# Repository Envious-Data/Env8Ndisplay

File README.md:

# Env8Ndisplay
 A 40x7 display using x4 is37fl3130

## Info:
I designed a clock a while ago using 8x LTP-305s, LTP-305s and TIL-305s are both discontinued but I made a PCBA replica called DIY305, Ive also just put LEDs on a PCB in the same arangement which this repo is one of them.

I quite like character displays which is why I made this one, there is some demo code in the firmware folder that makes use of the pico SDK so wire it up to the a pico making sure VCC goes to 3V3 and not VBUS or VSYS unless you want to use a level shifter, a number of ICs can handle different logic level voltage if needed but this one tends to glitch out in my experience.

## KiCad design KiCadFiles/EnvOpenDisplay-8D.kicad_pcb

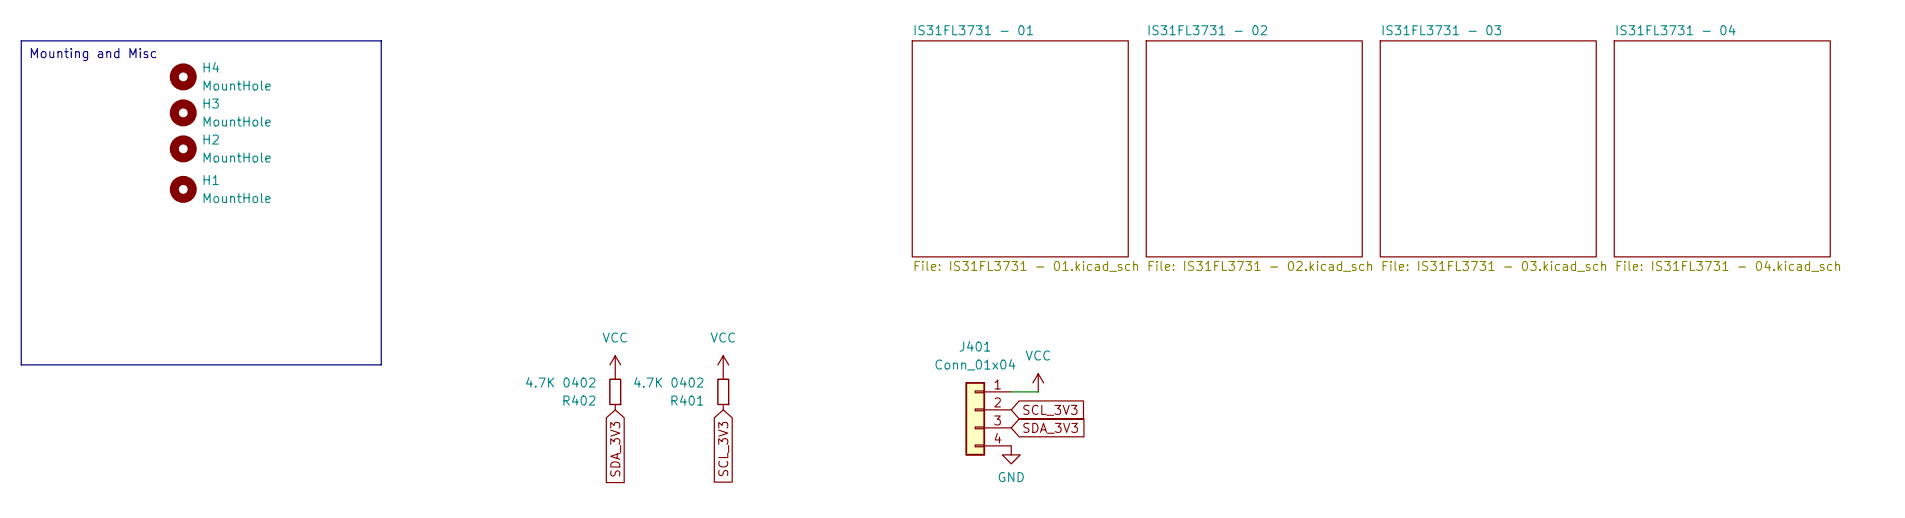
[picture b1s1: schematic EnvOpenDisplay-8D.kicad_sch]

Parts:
H1, H2, H3, H4: MountHole; MountingHole_2.2mm_M2
J401: Conn_01x04; PinSocket_1x04_P2.54mm_Vertical
R401, R402: 4.7K 0402; R_0402_1005Metric

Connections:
GND: J401.4; also elsewhere on the board
SCL_3V3: J401.2, R401.1; also elsewhere on the board
SDA_3V3: J401.3, R402.1; also elsewhere on the board
VCC: J401.1, R401.2, R402.2; also elsewhere on the board

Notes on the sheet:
Mounting and Misc

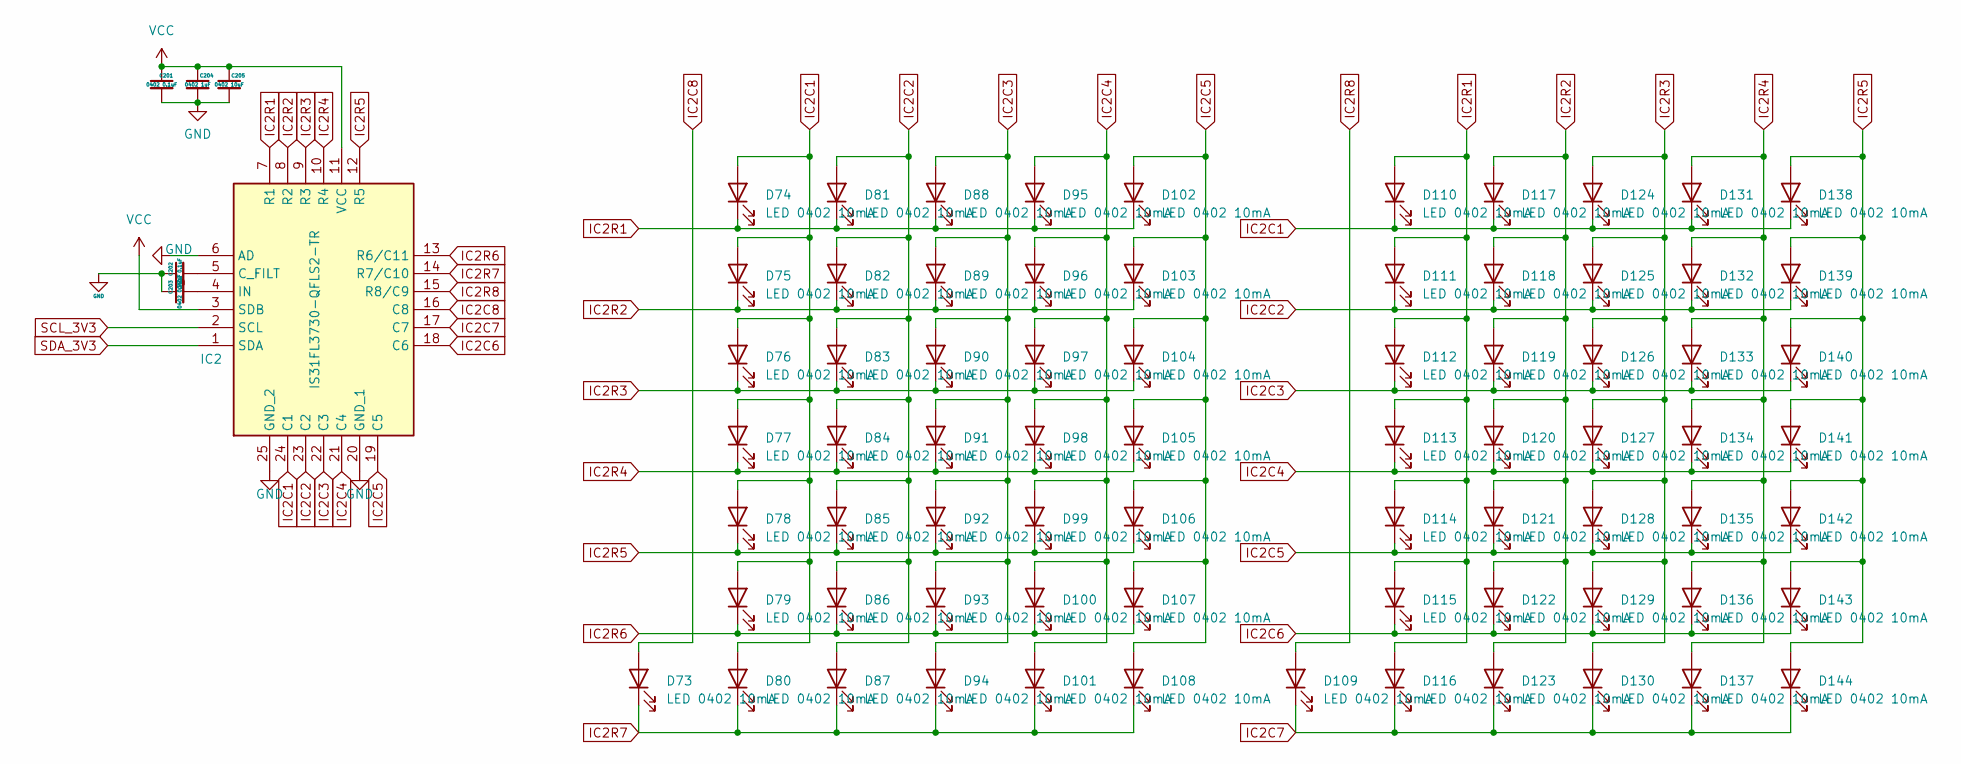
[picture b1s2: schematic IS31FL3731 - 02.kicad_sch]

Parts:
C201, C202: 0402 0.1uF; C_0402_1005Metric
C203: 0402 0.22uF; C_0402_1005Metric
C204: 0402 1uF; C_0402_1005Metric
C205: 0402 10uF; C_0402_1005Metric
D73, D74, D75, D76, D77, D78, D79, D80, D81, D82, D83, D84, D85, D86, D87, D88, D89, D90, D91, D92, D93, D94, D95, D96, D97, D98, D99, D100, D101, D102, D103, D104, D105, D106, D107, D108, D109, D110, D111, D112, D113, D114, D115, D116, D117, D118, D119, D120, D121, D122, D123, D124, D125, D126, D127, D128, D129, D130, D131, D132, D133, D134, D135, D136, D137, D138, D139, D140, D141, D142, D143, D144: LED 0402 10mA; LED_0402_1005Metric
IC2: IS31FL3730-QFLS2-TR; QFN-24-1EP_4x4mm_P0.5mm_EP2.6x2.6mm_ThermalVias; Mouser Part Number 870-IS31FL3730QFLS2R

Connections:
GND: C201.2, C202.1, C203.1, C204.2, C205.2, IC2.6 (AD), IC2.20 (GND_1), IC2.25 (GND_2); also elsewhere on the board
IC2C1: D74.2 (A), D75.2 (A), D76.2 (A), D77.2 (A), D78.2 (A), D79.2 (A), D80.2 (A), D110.1 (K), D117.1 (K), D124.1 (K), D131.1 (K), D138.1 (K), IC2.24 (C1)
IC2C2: D81.2 (A), D82.2 (A), D83.2 (A), D84.2 (A), D85.2 (A), D86.2 (A), D87.2 (A), D111.1 (K), D118.1 (K), D125.1 (K), D132.1 (K), D139.1 (K), IC2.23 (C2)
IC2C3: D88.2 (A), D89.2 (A), D90.2 (A), D91.2 (A), D92.2 (A), D93.2 (A), D94.2 (A), D112.1 (K), D119.1 (K), D126.1 (K), D133.1 (K), D140.1 (K), IC2.22 (C3)
IC2C4: D95.2 (A), D96.2 (A), D97.2 (A), D98.2 (A), D99.2 (A), D100.2 (A), D101.2 (A), D113.1 (K), D120.1 (K), D127.1 (K), D134.1 (K), D141.1 (K), IC2.21 (C4)
IC2C5: D102.2 (A), D103.2 (A), D104.2 (A), D105.2 (A), D106.2 (A), D107.2 (A), D108.2 (A), D114.1 (K), D121.1 (K), D128.1 (K), D135.1 (K), D142.1 (K), IC2.19 (C5)
IC2C6: D115.1 (K), D122.1 (K), D129.1 (K), D136.1 (K), D143.1 (K), IC2.18 (C6)
IC2C7: D109.1 (K), D116.1 (K), D123.1 (K), D130.1 (K), D137.1 (K), D144.1 (K), IC2.17 (C7)
IC2C8: D73.2 (A), IC2.16 (C8)
IC2R1: D74.1 (K), D81.1 (K), D88.1 (K), D95.1 (K), D102.1 (K), D110.2 (A), D111.2 (A), D112.2 (A), D113.2 (A), D114.2 (A), D115.2 (A), D116.2 (A), IC2.7 (R1)
IC2R2: D75.1 (K), D82.1 (K), D89.1 (K), D96.1 (K), D103.1 (K), D117.2 (A), D118.2 (A), D119.2 (A), D120.2 (A), D121.2 (A), D122.2 (A), D123.2 (A), IC2.8 (R2)
IC2R3: D76.1 (K), D83.1 (K), D90.1 (K), D97.1 (K), D104.1 (K), D124.2 (A), D125.2 (A), D126.2 (A), D127.2 (A), D128.2 (A), D129.2 (A), D130.2 (A), IC2.9 (R3)
IC2R4: D77.1 (K), D84.1 (K), D91.1 (K), D98.1 (K), D105.1 (K), D131.2 (A), D132.2 (A), D133.2 (A), D134.2 (A), D135.2 (A), D136.2 (A), D137.2 (A), IC2.10 (R4)
IC2R5: D78.1 (K), D85.1 (K), D92.1 (K), D99.1 (K), D106.1 (K), D138.2 (A), D139.2 (A), D140.2 (A), D141.2 (A), D142.2 (A), D143.2 (A), D144.2 (A), IC2.12 (R5)
IC2R6: D79.1 (K), D86.1 (K), D93.1 (K), D100.1 (K), D107.1 (K), IC2.13 (R6/C11)
IC2R7: D73.1 (K), D80.1 (K), D87.1 (K), D94.1 (K), D101.1 (K), D108.1 (K), IC2.14 (R7/C10)
IC2R8: D109.2 (A), IC2.15 (R8/C9)
unnamed: C202.2, IC2.5 (C_FILT)
unnamed: C203.2, IC2.4 (IN)
SCL_3V3: IC2.2 (SCL); also elsewhere on the board
SDA_3V3: IC2.1 (SDA); also elsewhere on the board
VCC: C201.1, C204.1, C205.1, IC2.3 (SDB), IC2.11 (VCC); also elsewhere on the board

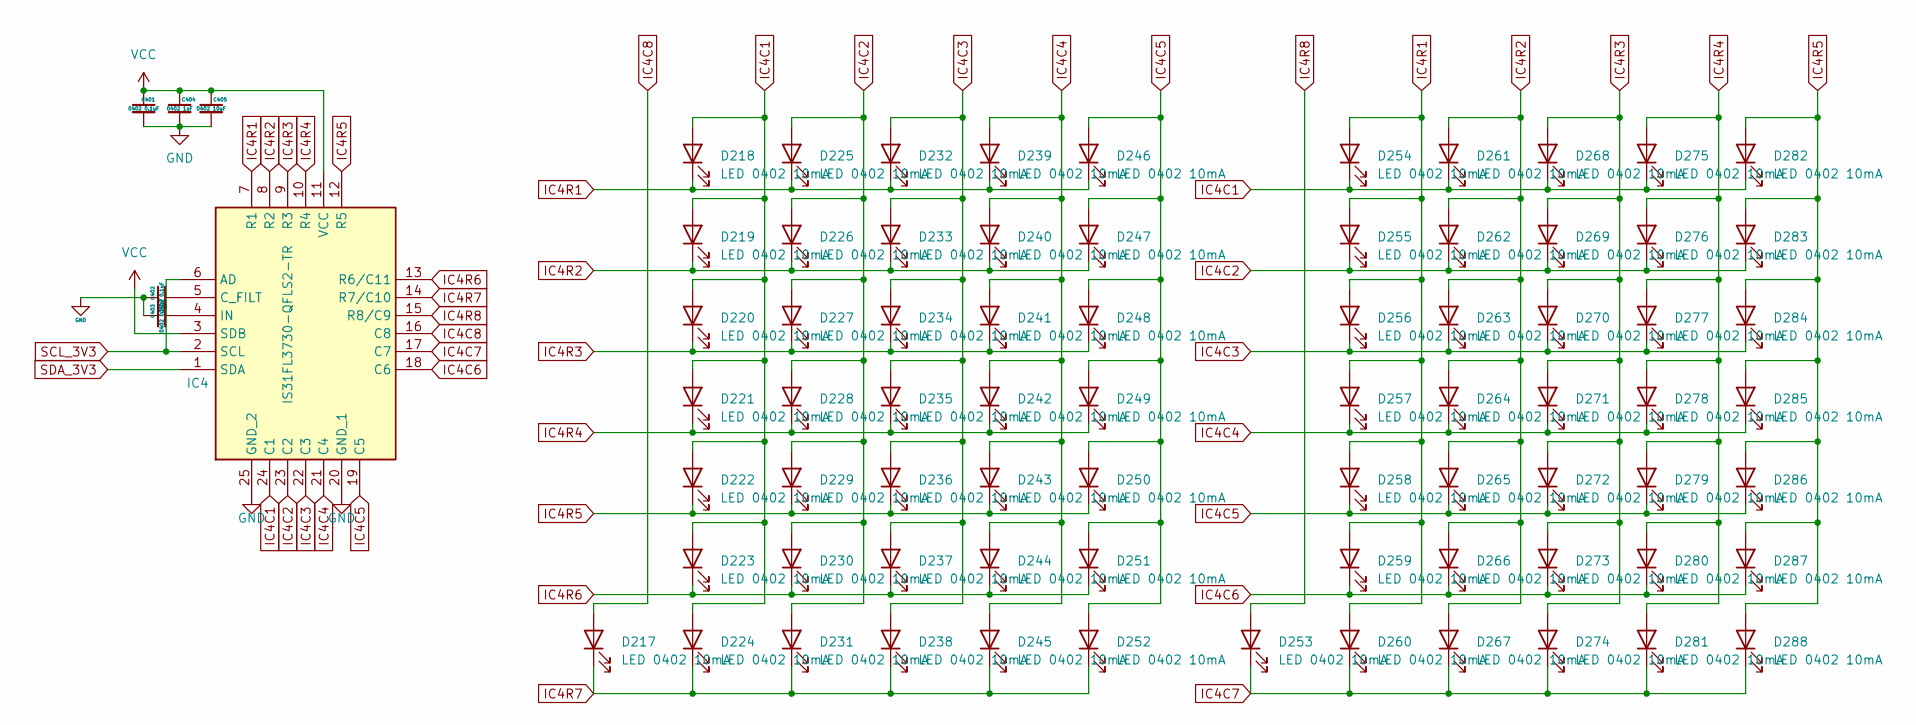
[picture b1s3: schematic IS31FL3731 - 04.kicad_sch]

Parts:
C401, C402: 0402 0.1uF; C_0402_1005Metric
C403: 0402 0.22uF; C_0402_1005Metric
C404: 0402 1uF; C_0402_1005Metric
C405: 0402 10uF; C_0402_1005Metric
D217, D218, D219, D220, D221, D222, D223, D224, D225, D226, D227, D228, D229, D230, D231, D232, D233, D234, D235, D236, D237, D238, D239, D240, D241, D242, D243, D244, D245, D246, D247, D248, D249, D250, D251, D252, D253, D254, D255, D256, D257, D258, D259, D260, D261, D262, D263, D264, D265, D266, D267, D268, D269, D270, D271, D272, D273, D274, D275, D276, D277, D278, D279, D280, D281, D282, D283, D284, D285, D286, D287, D288: LED 0402 10mA; LED_0402_1005Metric
IC4: IS31FL3730-QFLS2-TR; QFN-24-1EP_4x4mm_P0.5mm_EP2.6x2.6mm_ThermalVias; Mouser Part Number 870-IS31FL3730QFLS2R

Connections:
GND: C401.2, C402.1, C403.1, C404.2, C405.2, IC4.20 (GND_1), IC4.25 (GND_2); also elsewhere on the board
IC4C1: D218.2 (A), D219.2 (A), D220.2 (A), D221.2 (A), D222.2 (A), D223.2 (A), D224.2 (A), D254.1 (K), D261.1 (K), D268.1 (K), D275.1 (K), D282.1 (K), IC4.24 (C1)
IC4C2: D225.2 (A), D226.2 (A), D227.2 (A), D228.2 (A), D229.2 (A), D230.2 (A), D231.2 (A), D255.1 (K), D262.1 (K), D269.1 (K), D276.1 (K), D283.1 (K), IC4.23 (C2)
IC4C3: D232.2 (A), D233.2 (A), D234.2 (A), D235.2 (A), D236.2 (A), D237.2 (A), D238.2 (A), D256.1 (K), D263.1 (K), D270.1 (K), D277.1 (K), D284.1 (K), IC4.22 (C3)
IC4C4: D239.2 (A), D240.2 (A), D241.2 (A), D242.2 (A), D243.2 (A), D244.2 (A), D245.2 (A), D257.1 (K), D264.1 (K), D271.1 (K), D278.1 (K), D285.1 (K), IC4.21 (C4)
IC4C5: D246.2 (A), D247.2 (A), D248.2 (A), D249.2 (A), D250.2 (A), D251.2 (A), D252.2 (A), D258.1 (K), D265.1 (K), D272.1 (K), D279.1 (K), D286.1 (K), IC4.19 (C5)
IC4C6: D259.1 (K), D266.1 (K), D273.1 (K), D280.1 (K), D287.1 (K), IC4.18 (C6)
IC4C7: D253.1 (K), D260.1 (K), D267.1 (K), D274.1 (K), D281.1 (K), D288.1 (K), IC4.17 (C7)
IC4C8: D217.2 (A), IC4.16 (C8)
IC4R1: D218.1 (K), D225.1 (K), D232.1 (K), D239.1 (K), D246.1 (K), D254.2 (A), D255.2 (A), D256.2 (A), D257.2 (A), D258.2 (A), D259.2 (A), D260.2 (A), IC4.7 (R1)
IC4R2: D219.1 (K), D226.1 (K), D233.1 (K), D240.1 (K), D247.1 (K), D261.2 (A), D262.2 (A), D263.2 (A), D264.2 (A), D265.2 (A), D266.2 (A), D267.2 (A), IC4.8 (R2)
IC4R3: D220.1 (K), D227.1 (K), D234.1 (K), D241.1 (K), D248.1 (K), D268.2 (A), D269.2 (A), D270.2 (A), D271.2 (A), D272.2 (A), D273.2 (A), D274.2 (A), IC4.9 (R3)
IC4R4: D221.1 (K), D228.1 (K), D235.1 (K), D242.1 (K), D249.1 (K), D275.2 (A), D276.2 (A), D277.2 (A), D278.2 (A), D279.2 (A), D280.2 (A), D281.2 (A), IC4.10 (R4)
IC4R5: D222.1 (K), D229.1 (K), D236.1 (K), D243.1 (K), D250.1 (K), D282.2 (A), D283.2 (A), D284.2 (A), D285.2 (A), D286.2 (A), D287.2 (A), D288.2 (A), IC4.12 (R5)
IC4R6: D223.1 (K), D230.1 (K), D237.1 (K), D244.1 (K), D251.1 (K), IC4.13 (R6/C11)
IC4R7: D217.1 (K), D224.1 (K), D231.1 (K), D238.1 (K), D245.1 (K), D252.1 (K), IC4.14 (R7/C10)
IC4R8: D253.2 (A), IC4.15 (R8/C9)
unnamed: C402.2, IC4.5 (C_FILT)
unnamed: C403.2, IC4.4 (IN)
SCL_3V3: IC4.2 (SCL), IC4.6 (AD); also elsewhere on the board
SDA_3V3: IC4.1 (SDA); also elsewhere on the board
VCC: C401.1, C404.1, C405.1, IC4.3 (SDB), IC4.11 (VCC); also elsewhere on the board

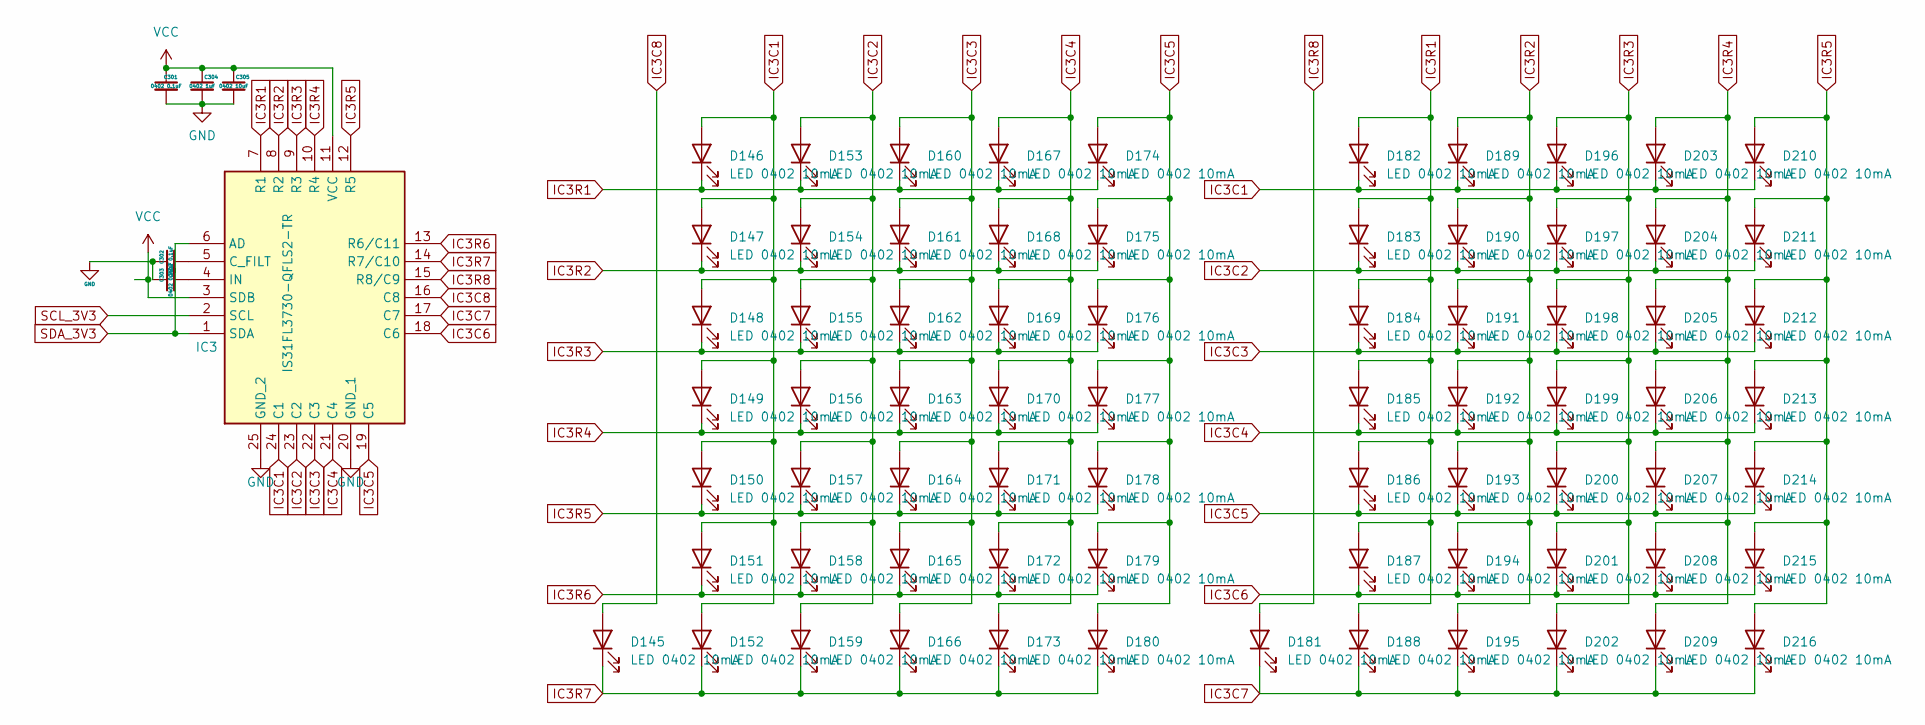
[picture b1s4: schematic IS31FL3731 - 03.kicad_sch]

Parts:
C301, C302: 0402 0.1uF; C_0402_1005Metric
C303: 0402 0.22uF; C_0402_1005Metric
C304: 0402 1uF; C_0402_1005Metric
C305: 0402 10uF; C_0402_1005Metric
D145, D146, D147, D148, D149, D150, D151, D152, D153, D154, D155, D156, D157, D158, D159, D160, D161, D162, D163, D164, D165, D166, D167, D168, D169, D170, D171, D172, D173, D174, D175, D176, D177, D178, D179, D180, D181, D182, D183, D184, D185, D186, D187, D188, D189, D190, D191, D192, D193, D194, D195, D196, D197, D198, D199, D200, D201, D202, D203, D204, D205, D206, D207, D208, D209, D210, D211, D212, D213, D214, D215, D216: LED 0402 10mA; LED_0402_1005Metric
IC3: IS31FL3730-QFLS2-TR; QFN-24-1EP_4x4mm_P0.5mm_EP2.6x2.6mm_ThermalVias; Mouser Part Number 870-IS31FL3730QFLS2R

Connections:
GND: C301.2, C302.1, C303.1, C304.2, C305.2, IC3.20 (GND_1), IC3.25 (GND_2); also elsewhere on the board
IC3C1: D146.2 (A), D147.2 (A), D148.2 (A), D149.2 (A), D150.2 (A), D151.2 (A), D152.2 (A), D182.1 (K), D189.1 (K), D196.1 (K), D203.1 (K), D210.1 (K), IC3.24 (C1)
IC3C2: D153.2 (A), D154.2 (A), D155.2 (A), D156.2 (A), D157.2 (A), D158.2 (A), D159.2 (A), D183.1 (K), D190.1 (K), D197.1 (K), D204.1 (K), D211.1 (K), IC3.23 (C2)
IC3C3: D160.2 (A), D161.2 (A), D162.2 (A), D163.2 (A), D164.2 (A), D165.2 (A), D166.2 (A), D184.1 (K), D191.1 (K), D198.1 (K), D205.1 (K), D212.1 (K), IC3.22 (C3)
IC3C4: D167.2 (A), D168.2 (A), D169.2 (A), D170.2 (A), D171.2 (A), D172.2 (A), D173.2 (A), D185.1 (K), D192.1 (K), D199.1 (K), D206.1 (K), D213.1 (K), IC3.21 (C4)
IC3C5: D174.2 (A), D175.2 (A), D176.2 (A), D177.2 (A), D178.2 (A), D179.2 (A), D180.2 (A), D186.1 (K), D193.1 (K), D200.1 (K), D207.1 (K), D214.1 (K), IC3.19 (C5)
IC3C6: D187.1 (K), D194.1 (K), D201.1 (K), D208.1 (K), D215.1 (K), IC3.18 (C6)
IC3C7: D181.1 (K), D188.1 (K), D195.1 (K), D202.1 (K), D209.1 (K), D216.1 (K), IC3.17 (C7)
IC3C8: D145.2 (A), IC3.16 (C8)
IC3R1: D146.1 (K), D153.1 (K), D160.1 (K), D167.1 (K), D174.1 (K), D182.2 (A), D183.2 (A), D184.2 (A), D185.2 (A), D186.2 (A), D187.2 (A), D188.2 (A), IC3.7 (R1)
IC3R2: D147.1 (K), D154.1 (K), D161.1 (K), D168.1 (K), D175.1 (K), D189.2 (A), D190.2 (A), D191.2 (A), D192.2 (A), D193.2 (A), D194.2 (A), D195.2 (A), IC3.8 (R2)
IC3R3: D148.1 (K), D155.1 (K), D162.1 (K), D169.1 (K), D176.1 (K), D196.2 (A), D197.2 (A), D198.2 (A), D199.2 (A), D200.2 (A), D201.2 (A), D202.2 (A), IC3.9 (R3)
IC3R4: D149.1 (K), D156.1 (K), D163.1 (K), D170.1 (K), D177.1 (K), D203.2 (A), D204.2 (A), D205.2 (A), D206.2 (A), D207.2 (A), D208.2 (A), D209.2 (A), IC3.10 (R4)
IC3R5: D150.1 (K), D157.1 (K), D164.1 (K), D171.1 (K), D178.1 (K), D210.2 (A), D211.2 (A), D212.2 (A), D213.2 (A), D214.2 (A), D215.2 (A), D216.2 (A), IC3.12 (R5)
IC3R6: D151.1 (K), D158.1 (K), D165.1 (K), D172.1 (K), D179.1 (K), IC3.13 (R6/C11)
IC3R7: D145.1 (K), D152.1 (K), D159.1 (K), D166.1 (K), D173.1 (K), D180.1 (K), IC3.14 (R7/C10)
IC3R8: D181.2 (A), IC3.15 (R8/C9)
unnamed: C302.2, IC3.5 (C_FILT)
unnamed: C303.2, IC3.4 (IN)
SCL_3V3: IC3.2 (SCL); also elsewhere on the board
SDA_3V3: IC3.1 (SDA), IC3.6 (AD); also elsewhere on the board
VCC: C301.1, C304.1, C305.1, IC3.3 (SDB), IC3.11 (VCC); also elsewhere on the board

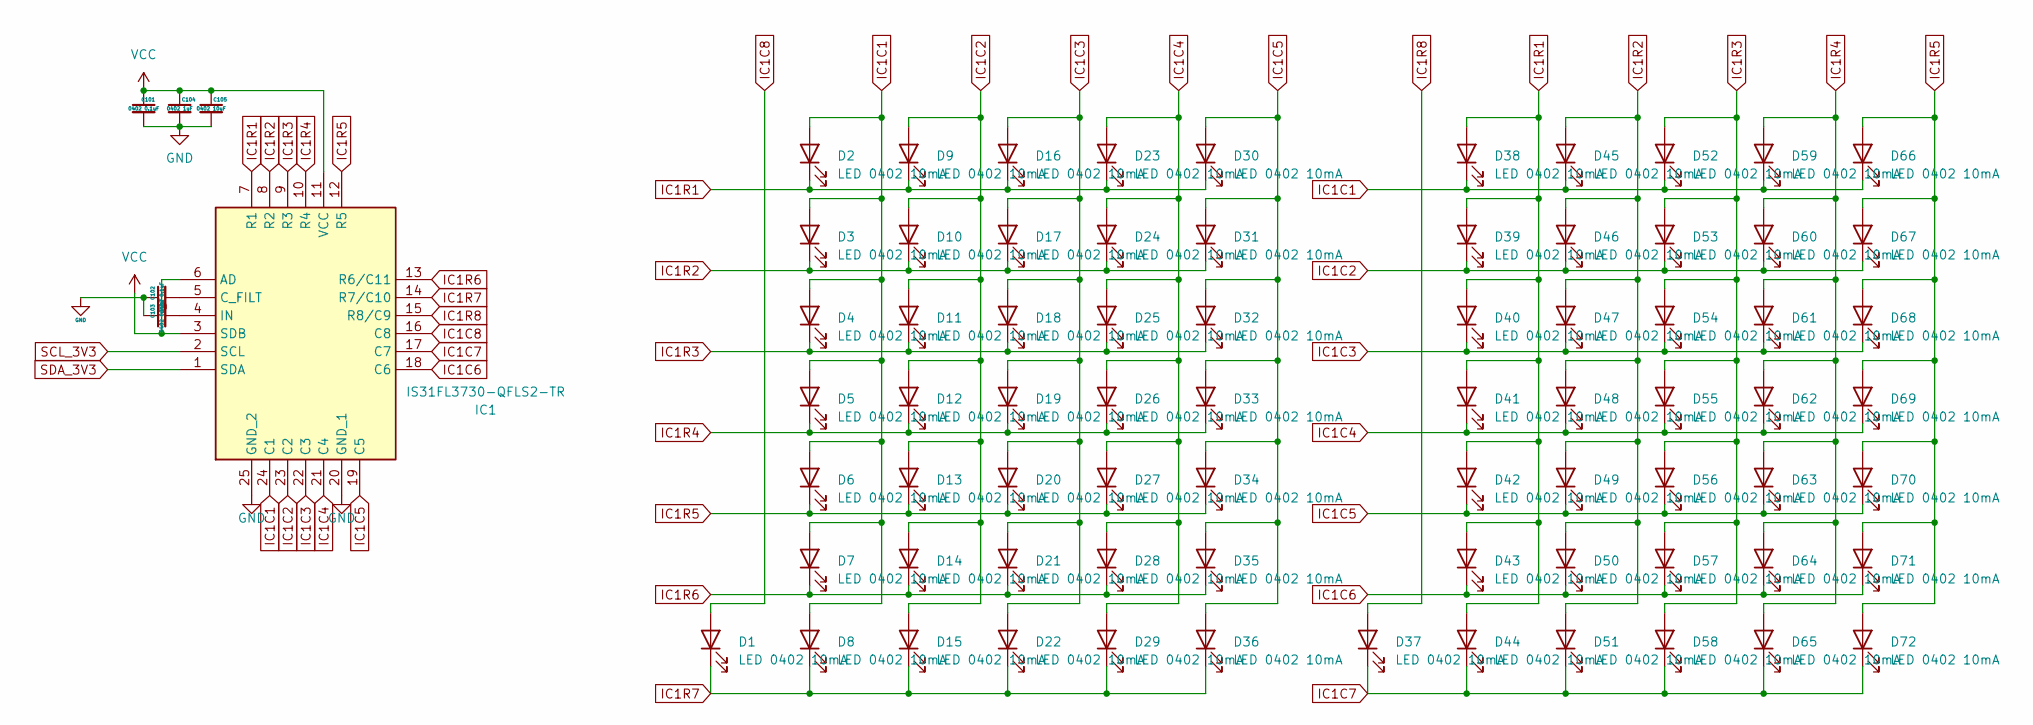
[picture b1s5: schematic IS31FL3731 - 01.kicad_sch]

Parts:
C101, C102: 0402 0.1uF; C_0402_1005Metric
C103: 0402 0.22uF; C_0402_1005Metric
C104: 0402 1uF; C_0402_1005Metric
C105: 0402 10uF; C_0402_1005Metric
D1, D2, D3, D4, D5, D6, D7, D8, D9, D10, D11, D12, D13, D14, D15, D16, D17, D18, D19, D20, D21, D22, D23, D24, D25, D26, D27, D28, D29, D30, D31, D32, D33, D34, D35, D36, D37, D38, D39, D40, D41, D42, D43, D44, D45, D46, D47, D48, D49, D50, D51, D52, D53, D54, D55, D56, D57, D58, D59, D60, D61, D62, D63, D64, D65, D66, D67, D68, D69, D70, D71, D72: LED 0402 10mA; LED_0402_1005Metric
IC1: IS31FL3730-QFLS2-TR; QFN-24-1EP_4x4mm_P0.5mm_EP2.6x2.6mm_ThermalVias; Mouser Part Number 870-IS31FL3730QFLS2R

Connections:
GND: C101.2, C102.1, C103.1, C104.2, C105.2, IC1.20 (GND_1), IC1.25 (GND_2); also elsewhere on the board
IC1C1: D2.2 (A), D3.2 (A), D4.2 (A), D5.2 (A), D6.2 (A), D7.2 (A), D8.2 (A), D38.1 (K), D45.1 (K), D52.1 (K), D59.1 (K), D66.1 (K), IC1.24 (C1)
IC1C2: D9.2 (A), D10.2 (A), D11.2 (A), D12.2 (A), D13.2 (A), D14.2 (A), D15.2 (A), D39.1 (K), D46.1 (K), D53.1 (K), D60.1 (K), D67.1 (K), IC1.23 (C2)
IC1C3: D16.2 (A), D17.2 (A), D18.2 (A), D19.2 (A), D20.2 (A), D21.2 (A), D22.2 (A), D40.1 (K), D47.1 (K), D54.1 (K), D61.1 (K), D68.1 (K), IC1.22 (C3)
IC1C4: D23.2 (A), D24.2 (A), D25.2 (A), D26.2 (A), D27.2 (A), D28.2 (A), D29.2 (A), D41.1 (K), D48.1 (K), D55.1 (K), D62.1 (K), D69.1 (K), IC1.21 (C4)
IC1C5: D30.2 (A), D31.2 (A), D32.2 (A), D33.2 (A), D34.2 (A), D35.2 (A), D36.2 (A), D42.1 (K), D49.1 (K), D56.1 (K), D63.1 (K), D70.1 (K), IC1.19 (C5)
IC1C6: D43.1 (K), D50.1 (K), D57.1 (K), D64.1 (K), D71.1 (K), IC1.18 (C6)
IC1C7: D37.1 (K), D44.1 (K), D51.1 (K), D58.1 (K), D65.1 (K), D72.1 (K), IC1.17 (C7)
IC1C8: D1.2 (A), IC1.16 (C8)
IC1R1: D2.1 (K), D9.1 (K), D16.1 (K), D23.1 (K), D30.1 (K), D38.2 (A), D39.2 (A), D40.2 (A), D41.2 (A), D42.2 (A), D43.2 (A), D44.2 (A), IC1.7 (R1)
IC1R2: D3.1 (K), D10.1 (K), D17.1 (K), D24.1 (K), D31.1 (K), D45.2 (A), D46.2 (A), D47.2 (A), D48.2 (A), D49.2 (A), D50.2 (A), D51.2 (A), IC1.8 (R2)
IC1R3: D4.1 (K), D11.1 (K), D18.1 (K), D25.1 (K), D32.1 (K), D52.2 (A), D53.2 (A), D54.2 (A), D55.2 (A), D56.2 (A), D57.2 (A), D58.2 (A), IC1.9 (R3)
IC1R4: D5.1 (K), D12.1 (K), D19.1 (K), D26.1 (K), D33.1 (K), D59.2 (A), D60.2 (A), D61.2 (A), D62.2 (A), D63.2 (A), D64.2 (A), D65.2 (A), IC1.10 (R4)
IC1R5: D6.1 (K), D13.1 (K), D20.1 (K), D27.1 (K), D34.1 (K), D66.2 (A), D67.2 (A), D68.2 (A), D69.2 (A), D70.2 (A), D71.2 (A), D72.2 (A), IC1.12 (R5)
IC1R6: D7.1 (K), D14.1 (K), D21.1 (K), D28.1 (K), D35.1 (K), IC1.13 (R6/C11)
IC1R7: D1.1 (K), D8.1 (K), D15.1 (K), D22.1 (K), D29.1 (K), D36.1 (K), IC1.14 (R7/C10)
IC1R8: D37.2 (A), IC1.15 (R8/C9)
unnamed: C102.2, IC1.5 (C_FILT)
unnamed: C103.2, IC1.4 (IN)
SCL_3V3: IC1.2 (SCL); also elsewhere on the board
SDA_3V3: IC1.1 (SDA); also elsewhere on the board
VCC: C101.1, C104.1, C105.1, IC1.3 (SDB), IC1.6 (AD), IC1.11 (VCC); also elsewhere on the board

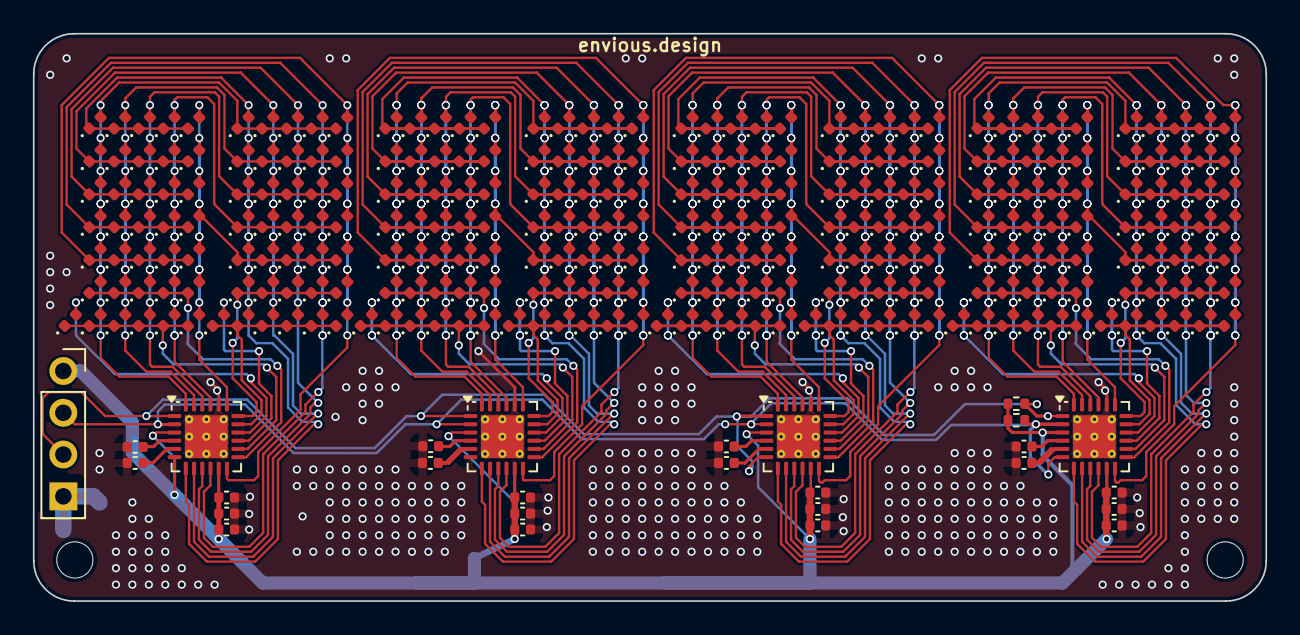
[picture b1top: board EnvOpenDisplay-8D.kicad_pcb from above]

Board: 2 copper layers, 75.0 x 34.5 mm, 317 parts (0 on the bottom side), 76 nets.

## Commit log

2025-04-22 initial commit+1
2025-06-23 updaertd the code to be a bit nicer and more functions, better font.
